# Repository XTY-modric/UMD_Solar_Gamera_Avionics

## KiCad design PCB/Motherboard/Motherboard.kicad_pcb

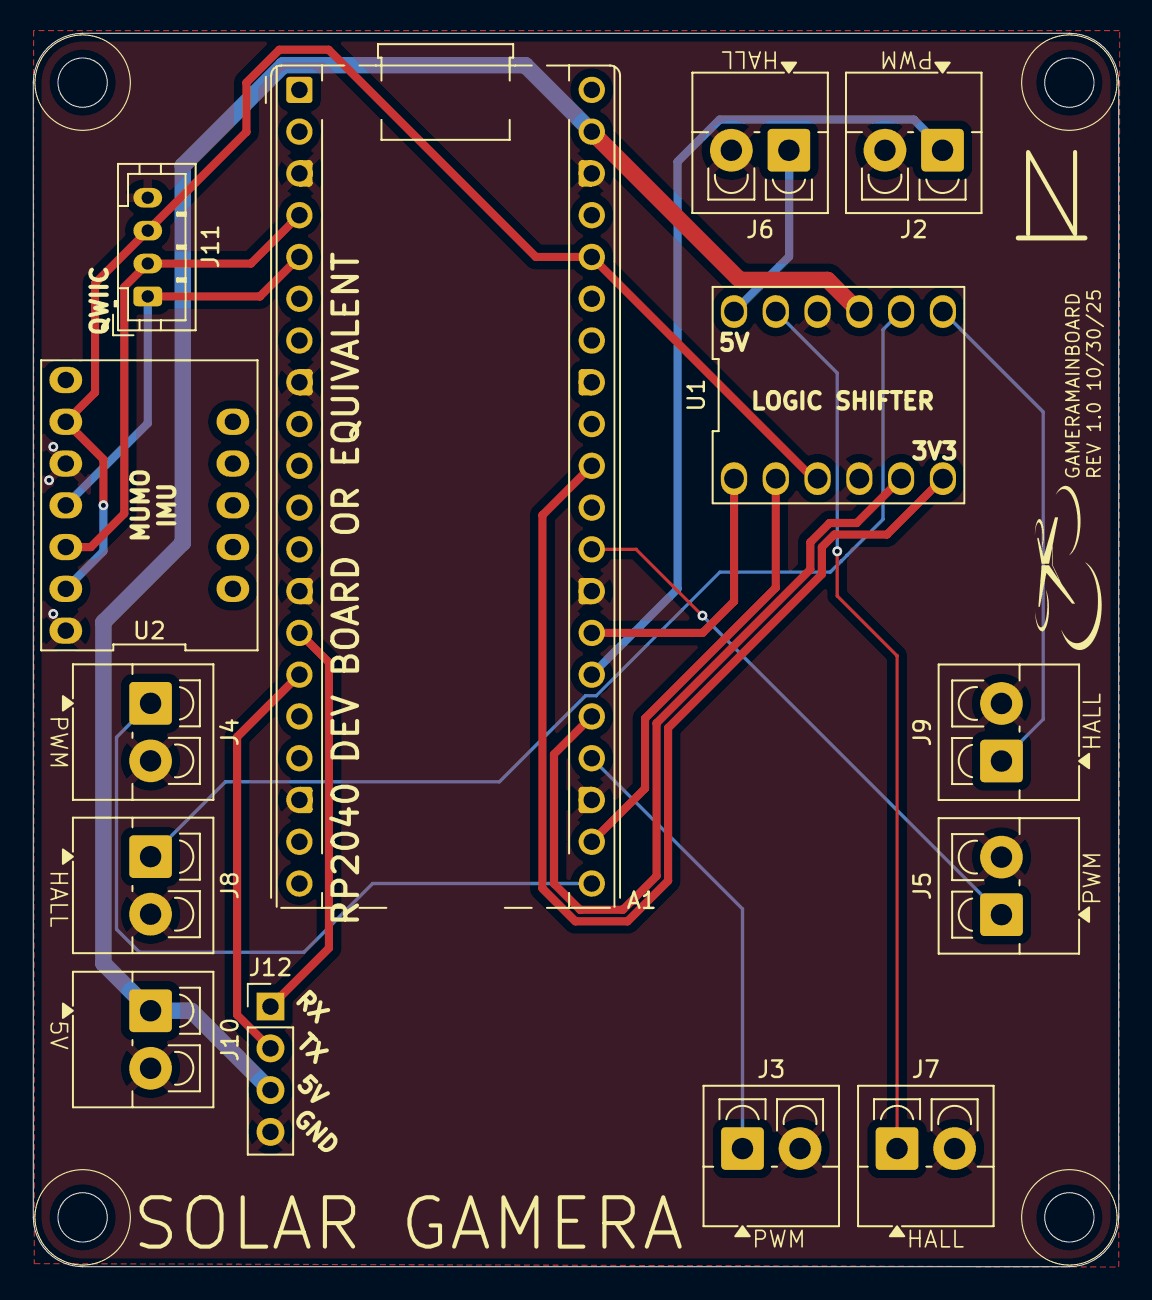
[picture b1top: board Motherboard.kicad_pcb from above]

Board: 2 copper layers, 66.0 x 75.0 mm, 14 parts (0 on the bottom side), 19 nets.

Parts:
A1: RaspberryPi_Pico; RaspberryPi_Pico_Common_THT
J2: North PWM; TerminalBlock_4Ucon_1x02_P3.50mm_Vertical
J3: South PWM; TerminalBlock_4Ucon_1x02_P3.50mm_Vertical
J4: East PWM; TerminalBlock_4Ucon_1x02_P3.50mm_Vertical
J5: West PWM; TerminalBlock_4Ucon_1x02_P3.50mm_Vertical
J6: North HALL; TerminalBlock_4Ucon_1x02_P3.50mm_Vertical
J7: South Hall; TerminalBlock_4Ucon_1x02_P3.50mm_Vertical
J8: East Hall; TerminalBlock_4Ucon_1x02_P3.50mm_Vertical
J9: West Hall; TerminalBlock_4Ucon_1x02_P3.50mm_Vertical
J10: Power; TerminalBlock_4Ucon_1x02_P3.50mm_Vertical
J11: QWIIC; JST_PH_B4B-PH-K_1x04_P2.00mm_Vertical
J12: Conn_01x04_Socket; PinHeader_1x04_P2.54mm_Vertical
U1: Logic Shifter
U2: Mumo

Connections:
+3V3: A1.36 (3V3), J11.3, U1.3 (LV), U2.7 (3V3), U2.11 (CS)
+5V: A1.39 (VSYS), J10.1, J12.3, U1.9 (HV)
EHALL3V3: A1.22 (GPIO17), U1.2 (LV2)
EHALL5V: J8.1, U1.8 (HV2)
EPWM: A1.21 (GPIO16), J4.1
GND: A1.3 (GND), A1.8 (GND), A1.13 (GND), A1.18 (GND), A1.23 (GND), A1.28 (GND), A1.38 (GND), J2.2, J3.2, J4.2, J5.2, J6.2, J7.2, J8.2, J9.2, J10.2, J11.4, J12.4, U1.4 (GND), U1.10 (GND), U2.8 (GND), U2.12 (SD0)
NHALL3V3: A1.31 (GPIO26_ADC0), U1.6 (LV4)
NHALL5V: J6.1, U1.12 (HV4)
NPWM: A1.26 (GPIO20), J2.1
RX: A1.14 (GPIO10), J12.1
SCL: A1.5 (GPIO3), J11.1, U2.9 (SCL)
SDA: A1.4 (GPIO2), J11.2, U2.10 (SDA)
SHALL3V3: A1.25 (GPIO19), U1.5 (LV3)
SHALL5V: J7.1, U1.11 (HV3)
SPWM: A1.24 (GPIO18), J3.1
TX: A1.15 (GPIO11), J12.2
WHALL3V3: A1.27 (GPIO21), U1.1 (LV1)
WHALL5V: J9.1, U1.7 (HV1)
WPWM: A1.29 (GPIO22), J5.1

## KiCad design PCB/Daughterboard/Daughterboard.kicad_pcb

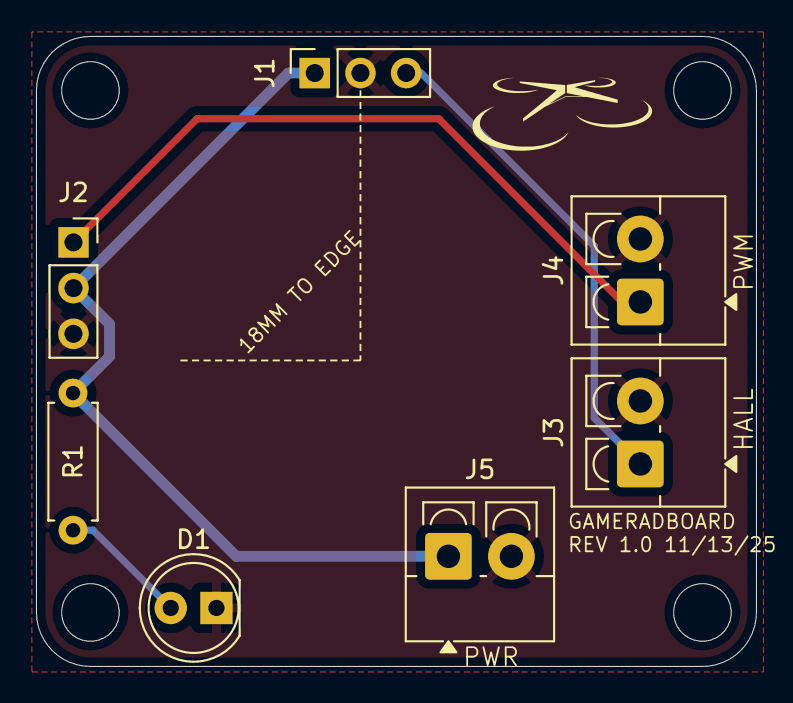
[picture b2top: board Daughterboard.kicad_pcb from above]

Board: 2 copper layers, 40.0 x 35.0 mm, 7 parts (0 on the bottom side), 5 nets.

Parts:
D1: LED; LED_D5.0mm
J1, J2: Conn_01x03_Pin; PinSocket_1x03_P2.54mm_Vertical
J3, J4, J5: Screw_Terminal_01x02; TerminalBlock_4Ucon_1x02_P3.50mm_Vertical
R1: R; R_Axial_DIN0207_L6.3mm_D2.5mm_P7.62mm_Horizontal

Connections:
+5V: J1.1, J2.2, J5.1, R1.2
ESC: J2.1, J4.1
GND: D1.1 (K), J1.2, J2.3, J3.2, J4.2, J5.2
HALL: J1.3, J3.1
unnamed: D1.2 (A), R1.1

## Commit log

2025-12-13 pcb tweaks and new gerbers
2026-02-23 refactored src for avionics with new things
2026-03-16 added missing readme
2026-03-24 Fix image loading and update main function structure
2026-04-21 Create User Interface
2026-04-21 Implement user interface with Dear PyGui
2026-04-21 Remove empty line at the beginning of User Interface file
2026-06-25 Newest version of the GUI
